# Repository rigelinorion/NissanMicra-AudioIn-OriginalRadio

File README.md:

# NissanMicra-AudioIn-OriginalRadio
CD changer emulator(audio in) for Nissan Micra k12 original radio

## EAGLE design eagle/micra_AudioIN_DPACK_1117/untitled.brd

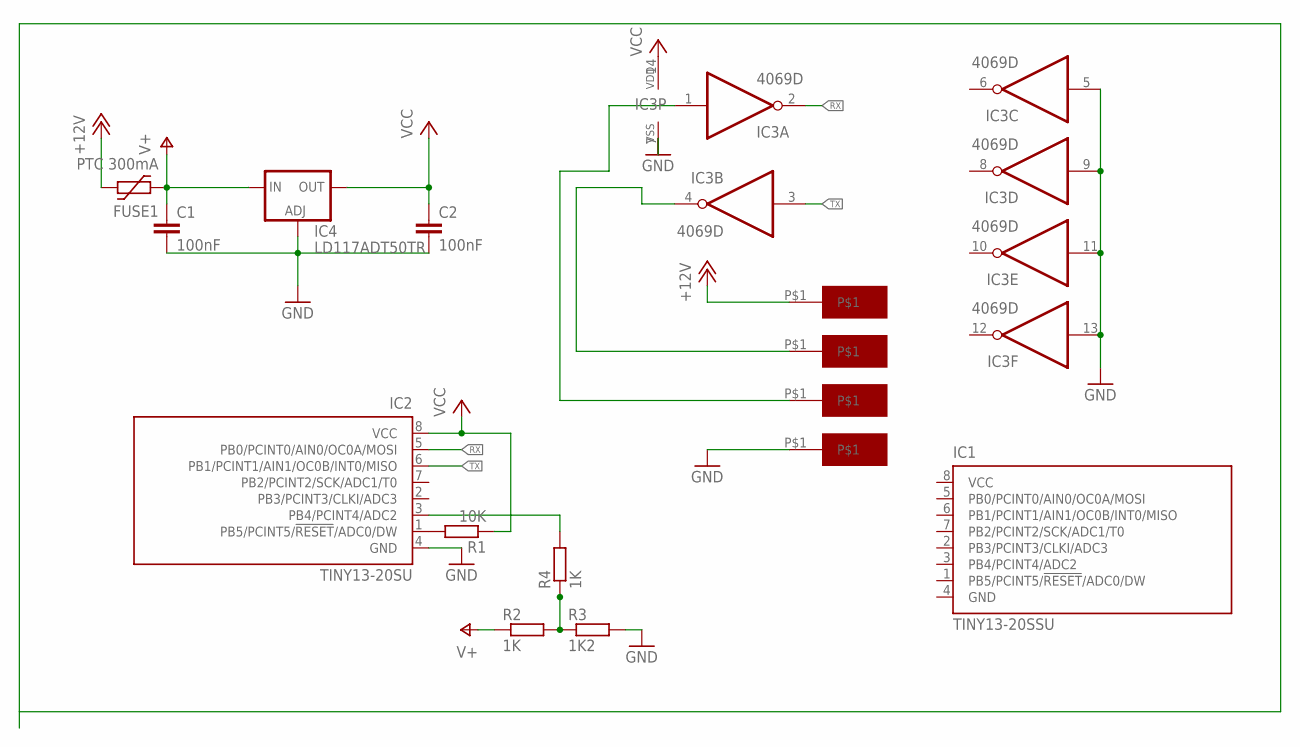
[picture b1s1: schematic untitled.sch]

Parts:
C1, C2: 100nF; C0805
FUSE1: PTC 300mA; 1206L
IC1: TINY13-20SSU; 8S1
IC2: TINY13-20SU; 8S2; MPN ATTINY13-20SSU
IC3: 4069D; SO14
IC4: LD117ADT50TR; DPACK
R1: 10K; R0805
R2, R4: 1K; R0805
R3: 1K2; R0805
U$1, U$2, U$3, U$4: WIRE_PAD_SMD; WIRE_SMD_PAD

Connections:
+12V: FUSE1.P$2 (2), U$1.P$1
GND: C1.2, C2.2, IC1.4 (GND), IC2.4 (GND), IC3.5 (I), IC3.7 (VSS), IC3.9 (I), IC3.11 (I), IC3.13 (I), IC4.1 (ADJ), R3.2, U$4.P$1
unnamed: IC2.1 (PB5/PCINT5/!RESET!/ADC0/DW), R1.2
unnamed: R2.2, R3.1, R4.1
unnamed: IC2.3 (PB4/PCINT4/ADC2), R4.2
unnamed: IC3.4 (O), U$2.P$1
unnamed: IC3.1 (I), U$3.P$1
RX: IC2.5 (PB0/PCINT0/AIN0/OC0A/MOSI), IC3.2 (O)
TX: IC2.6 (PB1/PCINT1/AIN1/OC0B/INT0/MISO), IC3.3 (I)
V+: C1.1, FUSE1.P$1 (1), IC4.3 (IN), R2.1
VCC: C2.1, IC1.8 (VCC), IC2.8 (VCC), IC3.14 (VDD), IC4.4 (OUT), R1.1

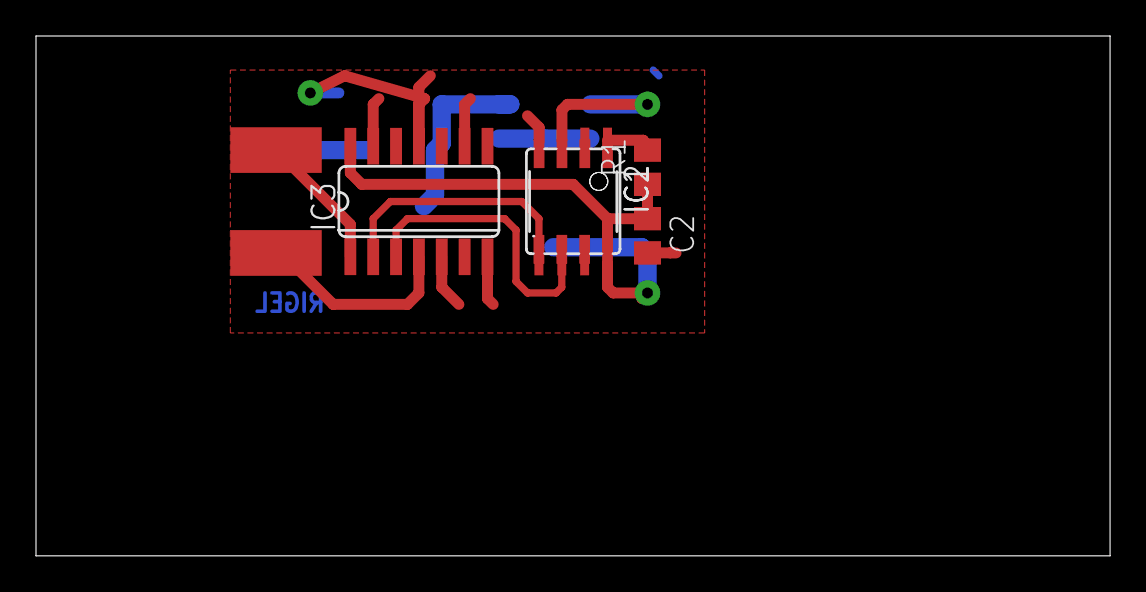
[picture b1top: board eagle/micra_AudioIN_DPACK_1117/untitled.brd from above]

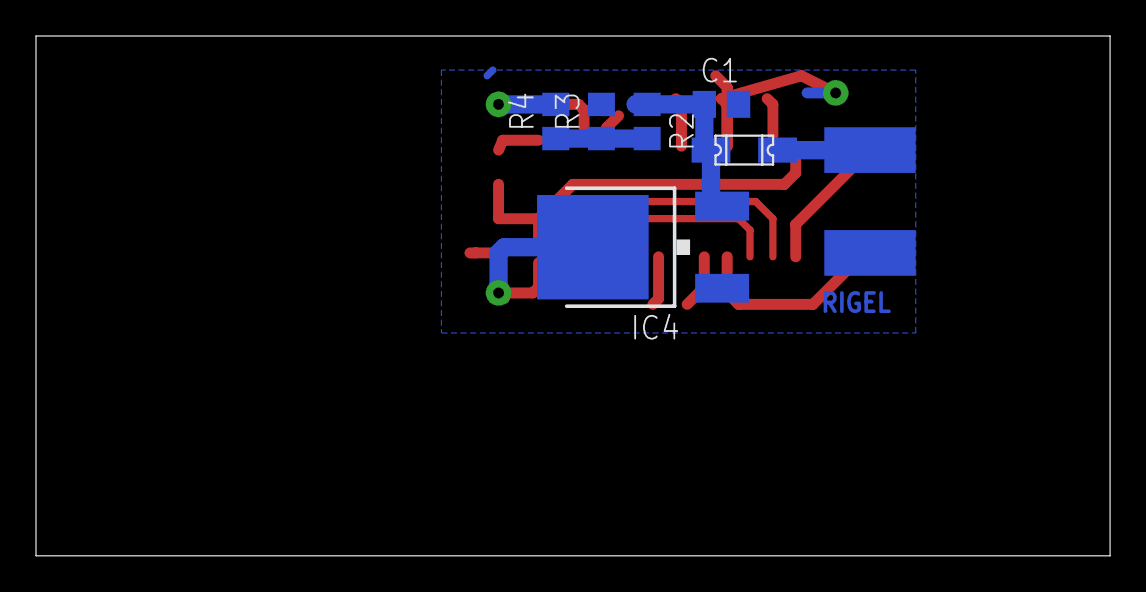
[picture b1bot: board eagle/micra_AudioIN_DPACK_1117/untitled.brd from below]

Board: 2 copper layers, 59.7 x 28.9 mm, 15 parts (8 on the bottom side), 11 nets.

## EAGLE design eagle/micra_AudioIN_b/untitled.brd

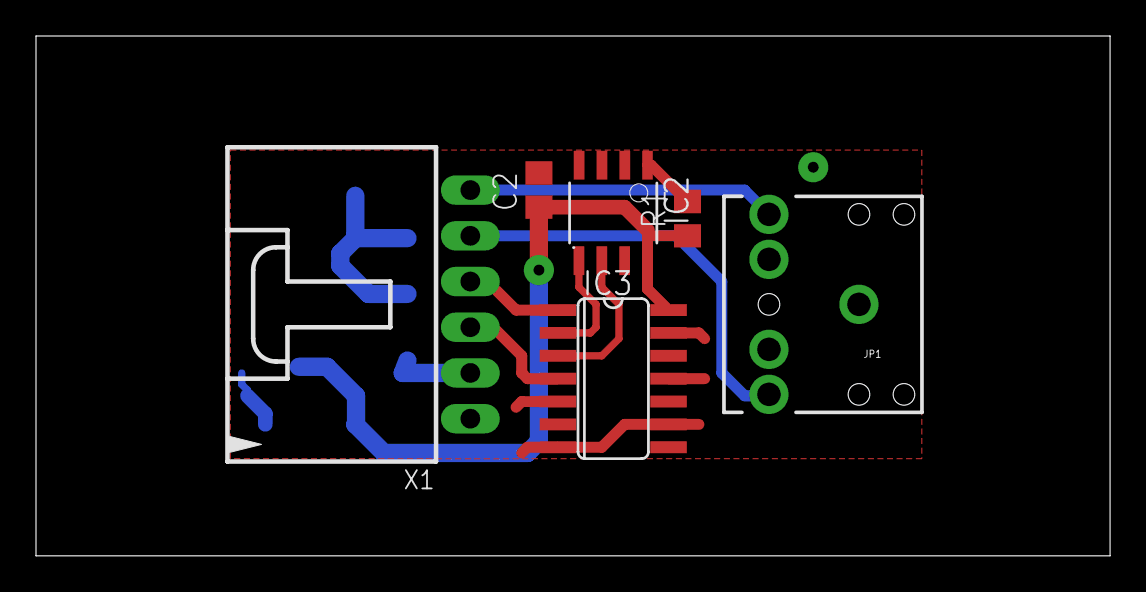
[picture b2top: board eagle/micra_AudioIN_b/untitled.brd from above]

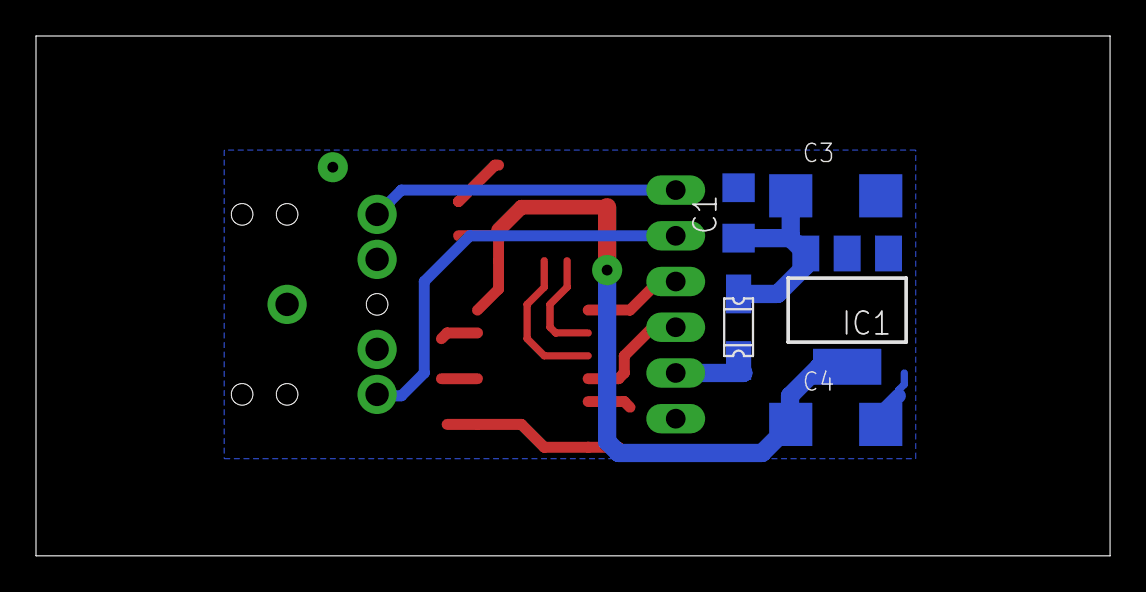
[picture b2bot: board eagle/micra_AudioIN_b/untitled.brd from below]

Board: 2 copper layers, 59.7 x 28.9 mm, 11 parts (5 on the bottom side), 11 nets.

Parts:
C1: 10nF; C1206
C2: 10nF; C0805
C3, C4: 10uF; SMC_C
FUSE1: PTC 300mA; 1206L
IC1: LD117AS50TR; SOT223
IC2: TINY13-20SSU; 8S1
IC3: 4069D; SO14
JP1: AUDIO-JACK
R1: 10K; R0805
X1: C-GRID-06-70553; 70553-06

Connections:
+12V: FUSE1.P$2, X1.2
GND: C1.2, C2.2, C3.-, C4.-, IC1.1, IC2.4, IC3.5, IC3.7, IC3.9, IC3.11, IC3.13, JP1.SLEEVE, X1.1
unnamed: IC2.1, R1.2
unnamed: JP1.RING, X1.5
unnamed: C1.1, C3.+, FUSE1.P$1, IC1.3
unnamed: JP1.TIP, X1.6
unnamed: IC3.4, X1.3
unnamed: IC3.1, X1.4
RX: IC2.5, IC3.2
TX: IC2.6, IC3.3
VCC: C2.1, C4.+, IC1.4, IC2.8, IC3.14, R1.1

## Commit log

2020-05-19 add files to repo

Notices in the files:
parts and their libraries:
SparkFun-Aesthetics: Licensing: Creative Commons ShareAlike 4.0 International - https://creativecommons.org/licenses/by-sa/4.0
